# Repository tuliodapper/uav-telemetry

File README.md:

# uav-telemetry
The purpose of this work is to provide a cost-effective method to gather important information of a flight for project validation. Because some of the data need to be gathered at a particular condition, it is desirable that the flight is constantly monitored in order to help the pilot to achieve a specified condition, e.g., altitude. To sum up, this work aims to build a platform responsible for collecting airspeed, orientation and altitude of a fixed-wing UAV flight, and current drained by the radio receiver and the servo actuators. In addition, the low-cost instrumentation system should be capable of acquiring, storing and transmitting these relevant flight parameters to a ground control station.

## Folders

### doc
Contains report, articles, presentation and video.

### software
Contains MATLAB code for the control panel interface, which aims to monitor the data collected from the acquisition board and transmitted to the ground station. Use MATLAB R2015a or later versions.

### firmware
Contains Arduino code and libraries for the firmware of the acquisition board.

### hardware
Contains the board and schematic EAGLE files for the hardware of the acquisition board.

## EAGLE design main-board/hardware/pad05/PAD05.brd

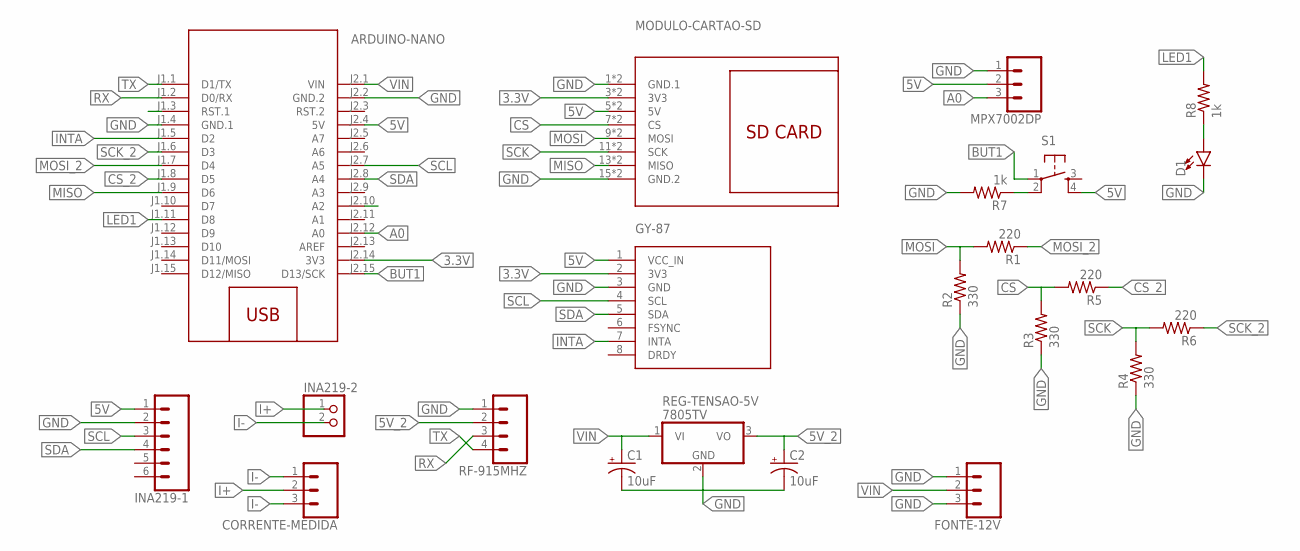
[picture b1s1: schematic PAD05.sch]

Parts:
ARDUINO-NANO: ARDUINO-NANO-3.0
C1, C2: 10uF; CPOL-RADIAL-2.5MM-5MM
CORRENTE-MEDIDA: CONN_03POLAR; MOLEX-1X3
D1: LED5MM; LED_5MM
FONTE-12V: CONN_03POLAR; MOLEX-1X3
GY-87: GY-86
INA219-1: CONN_06SILK_FEMALE_PTH; 1X06
INA219-2: PINHD-1X2; 1X02
MODULO-CARTAO-SD: CARD-SD-ADAPTER
MPX7002DP: CONN_03POLAR; MOLEX-1X3
R1, R5, R6: 220; 0204/7
R2, R3, R4: 330; 0204/7
R7, R8: 1k; 0204/7
REG-TENSAO-5V: 7805TV; TO220V
RF-915MHZ: CONN_04; 1X04
S1: TAC_SWITCHPTH; TACTILE-PTH

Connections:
3.3V: ARDUINO-NANO.J2.14 (3V3), GY-87.2 (3V3), MODULO-CARTAO-SD.3 (3V3), MODULO-CARTAO-SD.4 (3V3)
5V: ARDUINO-NANO.J1.3 (RST.1), ARDUINO-NANO.J2.4 (5V), GY-87.1 (VCC_IN), INA219-1.1, MODULO-CARTAO-SD.5 (5V), MODULO-CARTAO-SD.6 (5V), MPX7002DP.2, S1.4
5V_2: C2.1 (+), REG-TENSAO-5V.3 (VO), RF-915MHZ.2
A0: ARDUINO-NANO.J2.12 (A0), MPX7002DP.3
BUT1: ARDUINO-NANO.J2.15 (D13/SCK), S1.1
CS: MODULO-CARTAO-SD.7 (CS), MODULO-CARTAO-SD.8 (CS), R3.2, R5.2
CS_2: ARDUINO-NANO.J1.8 (D5), R5.1
GND: ARDUINO-NANO.J1.4 (GND.1), ARDUINO-NANO.J2.2 (GND.2), C1.2 (-), C2.2 (-), D1.K (C), FONTE-12V.1, FONTE-12V.3, GY-87.3 (GND), INA219-1.2, MODULO-CARTAO-SD.1 (GND.1), MODULO-CARTAO-SD.2 (GND.1), MODULO-CARTAO-SD.15 (GND.2), MODULO-CARTAO-SD.16 (GND.2), MPX7002DP.1, R2.1, R3.1, R4.1, R7.2, REG-TENSAO-5V.2 (GND), RF-915MHZ.1
I+: CORRENTE-MEDIDA.2, INA219-2.1
I-: CORRENTE-MEDIDA.1, CORRENTE-MEDIDA.3, INA219-2.2
INTA: ARDUINO-NANO.J1.5 (D2), ARDUINO-NANO.J2.10 (A2), GY-87.7 (INTA)
LED1: ARDUINO-NANO.J1.11 (D8), R8.2
MISO: ARDUINO-NANO.J1.9 (D6), MODULO-CARTAO-SD.13 (MISO), MODULO-CARTAO-SD.14 (MISO)
MOSI: MODULO-CARTAO-SD.9 (MOSI), MODULO-CARTAO-SD.10 (MOSI), R1.2, R2.2
MOSI_2: ARDUINO-NANO.J1.7 (D4), R1.1
unnamed: R7.1, S1.2
unnamed: D1.A, R8.1
RX: ARDUINO-NANO.J1.2 (D0/RX), RF-915MHZ.3
SCK: MODULO-CARTAO-SD.11 (SCK), MODULO-CARTAO-SD.12 (SCK), R4.2, R6.2
SCK_2: ARDUINO-NANO.J1.6 (D3), R6.1
SCL: ARDUINO-NANO.J2.7 (A5), GY-87.4 (SCL), INA219-1.3
SDA: ARDUINO-NANO.J2.8 (A4), GY-87.5 (SDA), INA219-1.4
TX: ARDUINO-NANO.J1.1 (D1/TX), RF-915MHZ.4
VIN: ARDUINO-NANO.J2.1 (VIN), C1.1 (+), FONTE-12V.2, REG-TENSAO-5V.1 (VI)

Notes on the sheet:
GY-87

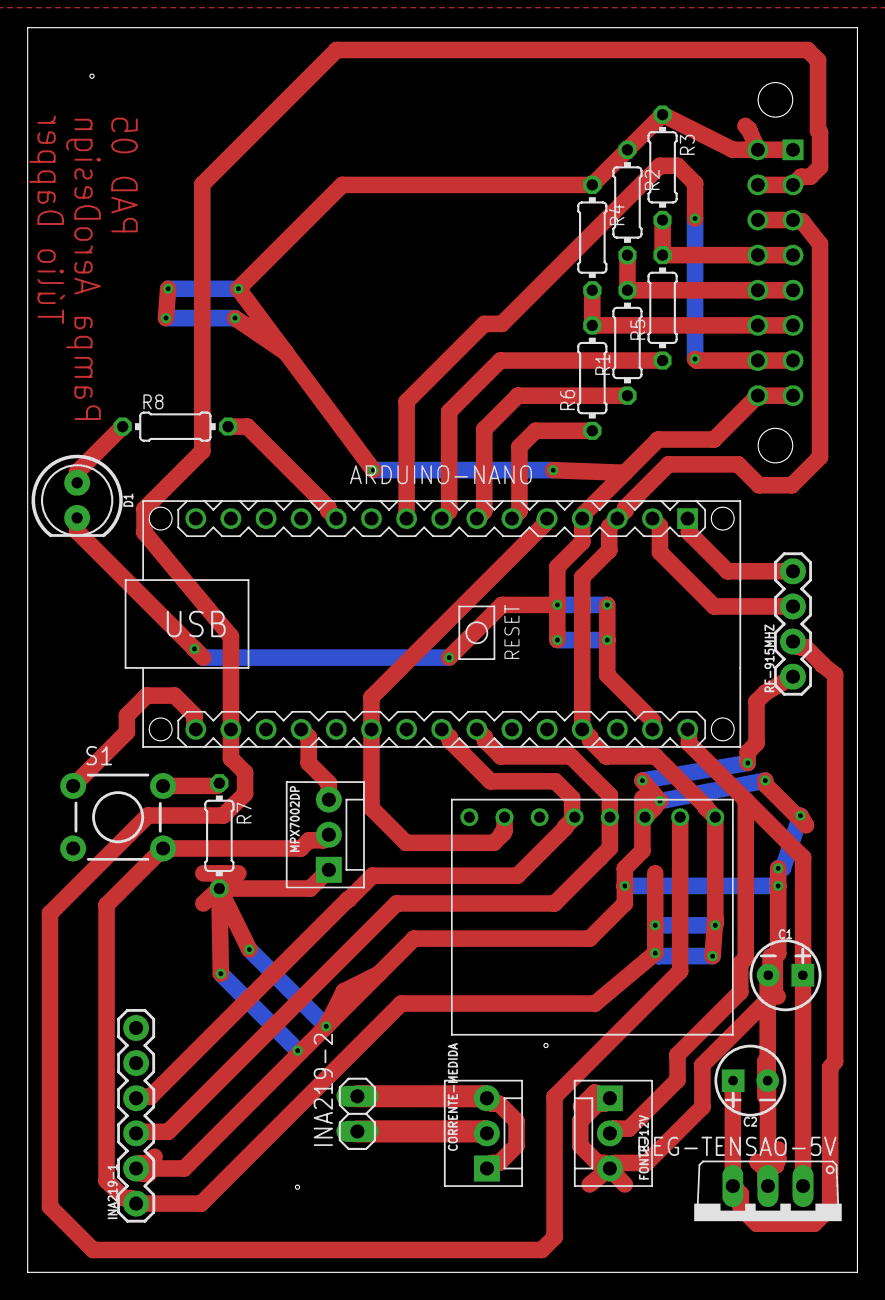
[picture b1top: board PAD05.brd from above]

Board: 2 copper layers, 60.0 x 90.0 mm, 22 parts (1 on the bottom side), 24 nets.

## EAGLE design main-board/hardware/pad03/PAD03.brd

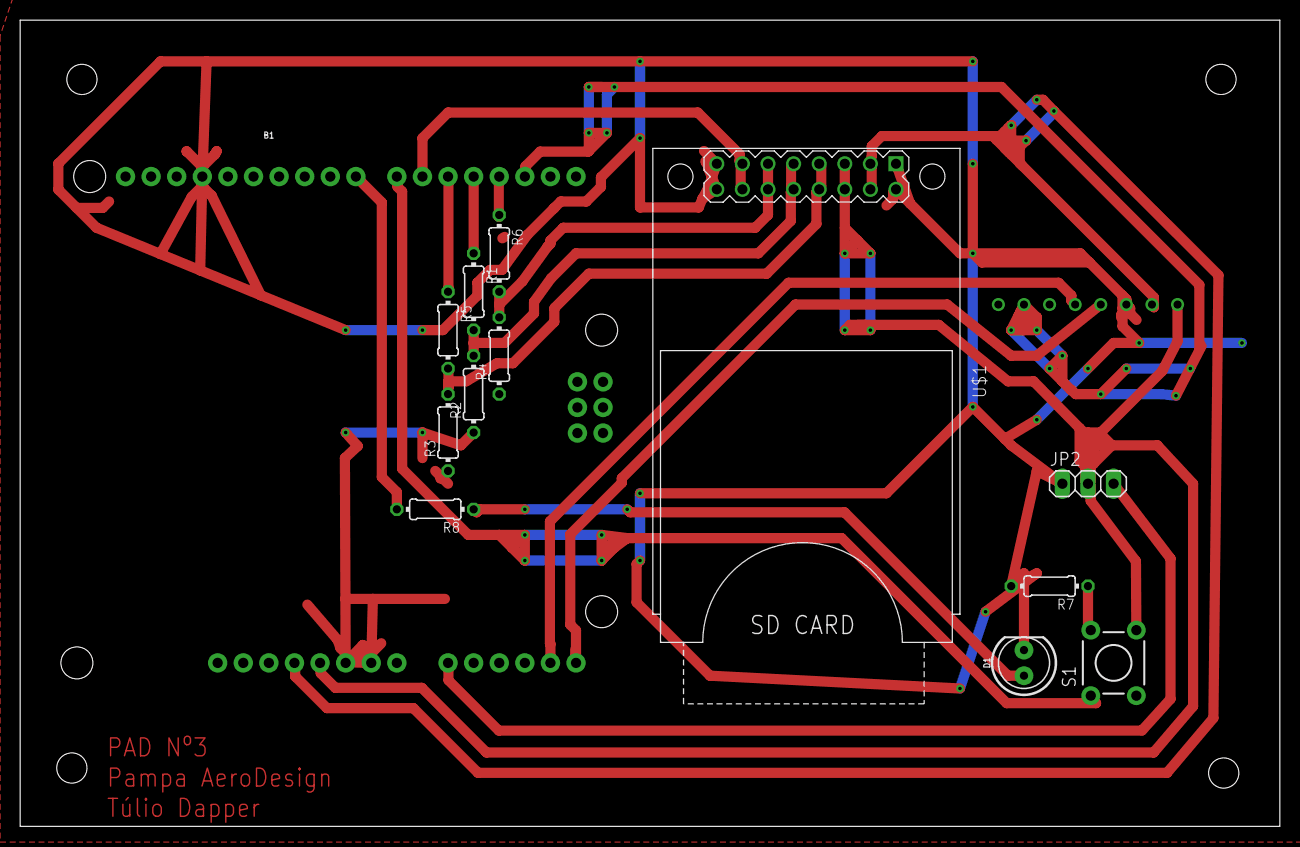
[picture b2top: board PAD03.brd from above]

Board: 2 copper layers, 125.0 x 80.0 mm, 14 parts (1 on the bottom side), 18 nets.

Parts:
B1: ARDUINO_UNO_R3; ARDUINO_R3
D1: LED_5MM
JP2: 1X03
R1, R5, R6: 220; 0204/7
R2, R3, R4: 330; 0204/7
R7, R8: 1k; 0204/7
S1: TACTILE-PTH
U$1: CARD-SD-ADAPTER
U$2: GY-86

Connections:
3.3V: B1.3.3V, U$1.3, U$1.4, U$2.2
5V: B1.5V, JP2.2, S1.4, U$1.5, U$1.6, U$2.1
A0: B1.A0, JP2.3
BUT1: B1.D7, S1.1
CS: R3.2, R5.2, U$1.7, U$1.8
CS_2: B1.D5, R5.1
GND: B1.GND@1, B1.GND@2, B1.GND@3, D1.K, JP2.1, R2.1, R3.1, R4.1, R7.2, U$1.1, U$1.2, U$1.15, U$1.16, U$2.3
INTA: B1.D2, U$2.7
LED1: B1.D8, R8.2
MISO: B1.D6, U$1.13, U$1.14
MOSI: R1.2, R2.2, U$1.9, U$1.10
MOSI_2: B1.D4, R1.1
unnamed: R7.1, S1.2
unnamed: D1.A, R8.1
SCK: R4.2, R6.2, U$1.11, U$1.12
SCK_2: B1.D3, R6.1
SCL: B1.A5, U$2.4
SDA: B1.A4, U$2.5

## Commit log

2019-01-30 1st commit

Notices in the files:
parts and their libraries:
SparkFun-Boards: Licensing: Creative Commons ShareAlike 4.0 International - https://creativecommons.org/licenses/by-sa/4.0
diy-modules: Released under the Creative Commons Attribution 4.0 International License: http://creativecommons.org/licenses/by/4.0
